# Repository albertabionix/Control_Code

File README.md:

CONTROL CODE

All files used in developing the control systems.
HardWare and Software

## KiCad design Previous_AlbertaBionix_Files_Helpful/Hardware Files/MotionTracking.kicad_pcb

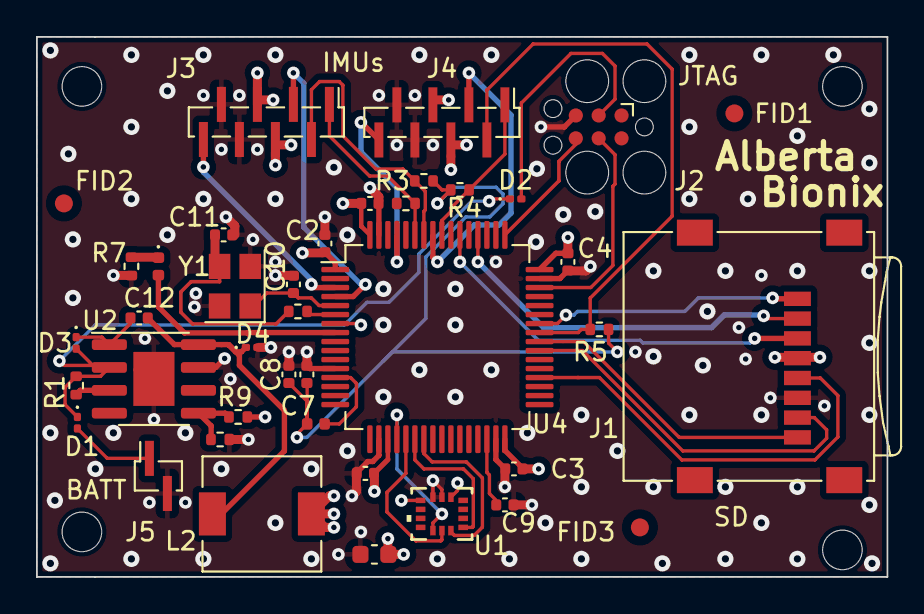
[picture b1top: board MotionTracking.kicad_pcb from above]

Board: 4 copper layers, 47.2 x 30.0 mm, 44 parts (0 on the bottom side), 37 nets.

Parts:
C1: 4.7u; C_0603_1608Metric
C2, C3, C4, C5, C6, C7: 100nF; C_0402_1005Metric
C8: 1uF; C_0402_1005Metric
C9: 47u?; C_0402_1005Metric
C10, C11: 2pF; C_0402_1005Metric
C12: 0.1uF; C_0402_1005Metric
D1, D2, D3, D4: D_Schottky; D_0201_0603Metric
D5: LED; LED_0402_1005Metric
FID1, FID2, FID3: Fiducial; Fiducial_1mm_Mask2mm
H1, H2, H3, H4: MountingHole; MountingHole_2.2mm_M2
J1: Micro_SD_Card_Det1; microSD_HC_Wuerth_693072010801
J2: Conn_ST_STDC14; Tag-Connect_TC2030-IDC-FP_2x03_P1.27mm_Vertical
J3, J4: Conn_01x08; PinSocket_1x08_P1.00mm_Vertical_SMD_Pin1Left
J5: Conn_01x02; PinSocket_1x02_P1.00mm_Vertical_SMD_Pin1Right
L1: 27nH; L_0402_1005Metric
L2: ~1.85uH; L_6.3x6.3_H3
R1: 3.17M; R_0402_1005Metric
R2: ??; R_0402_1005Metric
R3, R4, R5, R6: 10k; R_0402_1005Metric
R7: 220; R_0402_1005Metric
R8: 10.2k; R_0402_1005Metric
R9: 31.6k; R_0402_1005Metric
U1: LSM6DSV16XTR; LGA14L_LSM6_STM
U2: ADP2302ARDZ-3.3; SOIC-8-1EP_3.9x4.9mm_P1.27mm_EP2.29x3mm
U4: STM32F411RET6; LQFP-64_10x10mm_P0.5mm
Y1: 16MHz; Crystal_SMD_3225-4Pin_3.2x2.5mm

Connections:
5Vin: D2.2 (A), J2.3 (VCC)
+3.3V: C1.1, C2.1, C3.1, C4.1, C5.1, C6.1, J1.4 (VDD), J3.4, J3.5, J4.4, J4.5, L2.2, R9.2, U1.5 (VDD_IO), U1.8 (VDD), U4.1 (VBAT), U4.19 (VDD), U4.32 (VDD), U4.48 (VDD), U4.64 (VDD)
+3.3VA: C7.1, C8.1, L1.2, R3.1, R4.1, R5.2, R6.1
+BATT: D1.2 (A), J5.1
CS1: J3.3, U4.4 (PC15)
CS3: J4.3, U4.57 (PB5)
GND: C1.2, C2.2, C3.2, C4.2, C5.2, C6.2, C7.2, C8.2, C9.2, C10.2, C11.2, D4.2 (A), J1.6 (VSS), J2.5 (GND), J3.6, J3.7, J4.6, J4.7, J5.2, R7.2, R8.2, U1.6 (GND), U1.7 (GND), U2.7 (GND), U2.9 (PADGND), U4.12 (VSSA), U4.18 (VSS), U4.31 (VSS), U4.47 (VSS), U4.63 (VSS), Y1.2, Y1.4
HSE_IN: C10.1, U4.5 (PH0), Y1.1
HSE_OUT: R2.1, U4.6 (PH1)
I2C1_SCL: J3.2, R3.2, U4.58 (PB6)
I2C1_SDA: J3.1, R6.2, U4.59 (PB7)
I2C3_SCL: J4.2, R5.1, U4.41 (PA8)
I2C3_SDA: J4.1, R4.2, U4.56 (PB4)
unnamed: C11.1, R2.2, Y1.3
unnamed: D1.1 (K), D2.1 (K), D3.2 (A), R1.2, U2.2 (Vin)
unnamed: C12.1, D3.1 (K), U2.1 (BST)
unnamed: C12.2, D4.1 (K), L2.1, U2.8 (SW)
unnamed: D5.2 (A), U4.8 (PC0)
unnamed: D5.1 (K), R7.1
unnamed: U1.12 (CS), U4.20 (PA4)
unnamed: R1.1, U2.3 (EN)
unnamed: R8.1, R9.1, U2.5 (FB)
unnamed: C9.1, U4.30 (VCAP1)
SA1: J3.8, U4.3 (PC14)
SA3: J4.8, U4.61 (PB8)
SDIO_CK: J1.5 (CLK), U4.36 (PB15)
SDIO_CMD: J1.3 (CMD), U4.54 (PD2)
SDIO_D0: J1.7 (DAT0), U4.39 (PC8)
SDIO_D1: J1.8 (DAT1), U4.40 (PC9)
SDIO_D2: J1.1 (DAT2), U4.42 (PA9)
SDIO_D3: J1.2 (DAT3/CD), U4.52 (PC11)
SPI1_MISO: U1.1 (SDO/SA0), U4.22 (PA6)
SPI1_MOSI: U1.14 (SDA), U4.23 (PA7)
SPI1_SCK: U1.13 (SCL), U4.21 (PA5)
SWCLK: J2.6 (JCLK/SWCLK), U4.49 (PA14)
SWDIO: J2.4 (JTMS/SWDIO), U4.46 (PA13)
VS: L1.1, U4.13 (VDDA)

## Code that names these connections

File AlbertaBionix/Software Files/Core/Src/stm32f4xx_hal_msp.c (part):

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    /**SDIO GPIO Configuration
    PB10     ------> SDIO_D7
    PB14     ------> SDIO_D6
    PB15     ------> SDIO_CK
    PC8     ------> SDIO_D0
    PC9     ------> SDIO_D1
    PA9     ------> SDIO_D2
    PC11     ------> SDIO_D3
    PD2     ------> SDIO_CMD
    PB8     ------> SDIO_D4
    PB9     ------> SDIO_D5
    */
    GPIO_InitStruct.Pin = GPIO_PIN_10|GPIO_PIN_14|GPIO_PIN_15|GPIO_PIN_8
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    /**SDIO GPIO Configuration
    PB10     ------> SDIO_D7
    PB14     ------> SDIO_D6
    PB15     ------> SDIO_CK
    PC8     ------> SDIO_D0
    PC9     ------> SDIO_D1
    PA9     ------> SDIO_D2
    PC11     ------> SDIO_D3
    PD2     ------> SDIO_CMD
    PB8     ------> SDIO_D4
    PB9     ------> SDIO_D5
    */
    HAL_GPIO_DeInit(GPIOB, GPIO_PIN_10|GPIO_PIN_14|GPIO_PIN_15|GPIO_PIN_8
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
    __HAL_RCC_GPIOA_CLK_ENABLE();
    /**SPI1 GPIO Configuration
    PA5     ------> SPI1_SCK
    PA6     ------> SPI1_MISO
    PA7     ------> SPI1_MOSI
    */
    GPIO_InitStruct.Pin = GPIO_PIN_5|GPIO_PIN_6|GPIO_PIN_7;
    GPIO_InitStruct.Mode = GPIO_MODE_AF_PP;
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    /**SPI3 GPIO Configuration
    PB12     ------> SPI3_SCK
    PC12     ------> SPI3_MOSI
    PB4     ------> SPI3_MISO
    */
    GPIO_InitStruct.Pin = GPIO_PIN_12;
    GPIO_InitStruct.Mode = GPIO_MODE_AF_PP;
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    __HAL_RCC_SPI1_CLK_DISABLE();

    /**SPI1 GPIO Configuration
    PA5     ------> SPI1_SCK
    PA6     ------> SPI1_MISO
    PA7     ------> SPI1_MOSI
    */
    HAL_GPIO_DeInit(GPIOA, GPIO_PIN_5|GPIO_PIN_6|GPIO_PIN_7);

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    /**SPI3 GPIO Configuration
    PB12     ------> SPI3_SCK
    PC12     ------> SPI3_MOSI
    PB4     ------> SPI3_MISO
    */
    HAL_GPIO_DeInit(GPIOB, GPIO_PIN_12|GPIO_PIN_4);

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
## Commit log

2024-05-19 Uploaded Files from previous GitHub
    All files from git repository me and Uriah worked on. Some software files that might be useful are included. Also all the hardware is included.
2024-05-19 Changed Name of Folder
2024-05-19 Added Folders and some tests Ive worked on

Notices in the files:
AlbertaBionix/Software Files/Core/Src/stm32f4xx_hal_msp.c:
Copyright (c) 2024 STMicroelectronics.
All rights reserved.
This software is licensed under terms that can be found in the LICENSE file
